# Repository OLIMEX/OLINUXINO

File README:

OLinuXino - Single-Board Linux Computer, Copyright (C) 2012-2019, OLIMEX Ltd

THE PROJECT:

OLinuXino is an Open Source Software and Open Source Hardware project, aiming to produce low cost (starting from EUR 24)
Linux and Android Single Board Computers (SBC) in both commercial and industrial temperature range. Board variants with extra flash memory
are also available.

People keep comparing OLinuXino with Raspberry Pi and BeagleBone project, so we would like to state some of the differences here:

Although the projects are similar there are different goals and implementations:

OLINUXINO is completely open source - including hardware and software, this means you have access to all CAD files and sources and you
can reuse them for your own personal or commercial project. There are NO restrictions to manufacture and sell these board for your own 
use or resale, just keep credits that your board is based on OLinuXino design and make sure to change the silkscreen to not confuse people that you are selling original OLinuXino.

iMX233-OLINUXINO use widely available microcontroller iMX233 which cost USD 5.50 in 100 pcs quantity, this means that people can spin 
off their own boards and manufacture them cheap as the processor is in TQFP easy to assembly by hobbyist package.

RASPBERRY PI have not released CAD files nor complete schematics, RPi uses processor from Broadcom which is not available for sale in 
small quantity, it uses BGA package which require expensive setup to assembly. RPi is designed to be home gadget, OLINUXINO viarnatns
can work in industrial environment -25+85C and are designed to be low cost but NOISE immune.

BeagleBone have open source CAD hardware files but uses BGA processor and BB board is very complex and hard to manufacture in small 
quantities.

iMX233-OLINUXINO uses processor on 454Mhz and have less memory and will not allow fancy graphics, but this is not our intention.

To name few potential applications for OLINUXINO:

- 3D rep-rap printer controller including G-code interpreter - now all 3D printers use PC/Laptop connected to Arduino stepper driver, this board will handle both without problem
- Low cost PLC running open source PLC programming languages
- Home Automation - connecting GSM module or Zigbee sensors would be easy with the existing UEXT connector
- OLINUXINO has 100Mbit Ethernet port, but there are many low cost $10 WIFI USB modules with Linux drivers like RTL8192 which allow OLINUXINO to connect to internet wireless and to may control relays and sensors without need for LAN wiring.
- Having small linux module with GPIOs would be handy even to embed it in other products. BeagleBone do not allow the board to be used in commercial projects, there are no restrictions with OLINUXINO

THE DEVELOPMENT PATH:

Step 1:
OLinuXino project started with iMX233 from Freescale for several reasons: this is ARM9 processor running at 454Mhz with enough power to run linux and still in handsolder friendly TQFP package, which allow hobby DIY approach. iMX233-OLinuXino-MICRO is even on 2 layer PCB and running at full speed. The maximum memory of 64MB though limited the applications with it, so we were looking around for something more powerful when A13 from Allwinner came along.

Step 2:
A13 is Cortex-A8 processor which can address up to 512MB RAM and run at 1GHz. The best of all it again comes in the hand soldering friendly TQFP package (actually it's the first and the only Cortex-A8 in TQFP package). So designing A13-OLinuXino was the next logical step. The first prototypes are already produced and everything works as expected. A13-OLinuXino production is scheduled for September.
A13-OLinuXino have 512MB RAM, 4 USB hosts (1 dedicated for WIFI), 1 USB-OTG, Audio out, Audio in, SD-card, VGA, buttons, 72 GPIOs, LCD connector

Step 3:
A10 is the big brother of A13 it's also Cortex-A8 running at 1Ghz (many Chinese tablet/set-top-box vendors write it's 1.2 or 1.5GHz but this is overclocking and same is possible with A13 too, but not recommended for normal operation). It can address up to 2GB of RAM, and on top of A13 have SATA, HDMI, VGA and composite video outputs + much more GPIOs as it's in BGA442 package. While we developed A13-OLinuXino we got many requests for hackable A10 board as all current solutions are tablets or set-top-boxes which are not designed to have GPIO connectors and to allow hardware hacking
A10-OLinuXino will have same as A13 but including more GPIOs, 1GB RAM, HDMI, SATA and 100MBit Ethernet

Step 4:
A10S is new processor from Allwinner with Ethernet and HDMI. Low cost board with A10S Cortex-A8 @ 1GHz + 512MB RAM + Ethernet 100Mbit + USB Host/USB-OTG + SD-card + SD-MMC card + HDMI is released.

Step 5:
A20 is Dual Core Cortex-A7 processor which is almost pin to pin compatible, so A10 board can work with A20 processors too. We have low cost A20 board prototypes working and A20-SOM work in progress.

Step 6:
Texas Instruments Sitara AM3352 processor is necessary for Industrial customers who want a longevity supply program, TI as Freescale guarantee that when start producing processor continue the production at least 5-10 years, this way customers are not forced to change their designs every year. So we work on AM3352 module with: AM3352 720Mhz, Cortex-A8 processor, 512MB DDR3 RAM (optional we will make 1GB RAM version also), power supply 6-16VDC, x4 USB 2.0 hosts, 100Mbit Ethernet, SD-card, VGA, CAN, GPIO connector, LCD connector with touchscreen to work with A13-LCD7TS and A13-43TS LCDs, UEXT connector, JTAG.

Step 7:
Allwinner A64 chip into A64-OLinuXino development board.

Step 8:
DIY laptop TERES-I with A64 chip.

Step 9:
RT5350F-OLinuXino first MIPS OLinuXino with Ralink RT5350 
S3-OLinuXino camera linux board with Allwinner S3 SOC
STM32MP15X-OLinuXino-LIME2 - board with same layout as A20-OLinuXino-LIME2 but with STM new DUal Core Cortex-A7 processor STM32MP157
iMX8QM-TUKHLA - OLinuXino board with most powerful NXP iMX8 processor QUAD MAX with Dual core Cortex-A72 and Quad code Cortex-A53 

Step 10:
... we don't know yet, there are lot of candidates, but we start to become a little picky. To start the development of new OSHW OLinuXino board we will look at least the SOC to have proper Linux Support as we are really overwhelmed of the tons of new SOCs released with just Android and binary blobs.
Rockchip is doing a very good job recently releasing mainline Linux support for their devices.

WEB RESOURCES:

http://www.olimex.com - OLIMEX Ltd web site where the OLinuXino board info is hosted

https://github.com/OLIMEX/OLINUXINO - GitHub web site hosting the Hardware and Software sources

https://www.olimex.com/forum/index.php - Olimex forum for OLinuXino project discussions

OLinuXino IRC channel: join #olimex on irc.freenode.net , alternatively use http://webchat.freenode.net/?channels=olimex for web IRC chat

LICENSEE:

HARDWARE
The Hardware project is released under the Creative Commons Attribution-Share Alike 3.0 United States License.
You may reproduce it for both your own personal use, and for commercial use. 
You will have to provide a link to the original creator of the project http://www.olimex.com on any documentation or website.
You may also modify the files, but you must then release them as well under the same terms.
Credit can be attributed through a link to the creator website: http://www.olimex.com
You should alter the silkscreen to not confuse people who buy your product that they buy the original OLinuXino made by Olimex.

SOFTWARE
The software is released under GPL3.

DOCUMENTATION
The documentation is released under the Creative Commons Attribution-Share Alike 3.0 United States License.

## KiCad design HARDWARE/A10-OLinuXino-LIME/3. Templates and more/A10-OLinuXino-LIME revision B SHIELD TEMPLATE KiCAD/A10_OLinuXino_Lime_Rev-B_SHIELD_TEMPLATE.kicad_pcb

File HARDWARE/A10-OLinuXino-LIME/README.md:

## Olimex A10-OLinuXino-LIME hardware sources

## Product page: https://www.olimex.com/Products/OLinuXino/A10/A10-OLinuXino-LIME/open-source-hardware

## A20-OLINUXINO-LIME AND A10-OLINUXINO-LIME SHARE SAME HARDWARE LAYOUT. 

### FOR LATEST HARDWARE REVISION, PLEASE VISIT THE A20-OLINUXINO-LIME HARDWARE SECTION: 

### https://github.com/OLIMEX/OLINUXINO/tree/master/HARDWARE/A20-OLinuXino-LIME

### THE A10 AND A20 CHIPS ARE PIN-TO-PIN COMPATIBLE (DROP-IN REPLACEABLE). ONLY THE MAIN CHIP PLACED IS DIFFERENT.

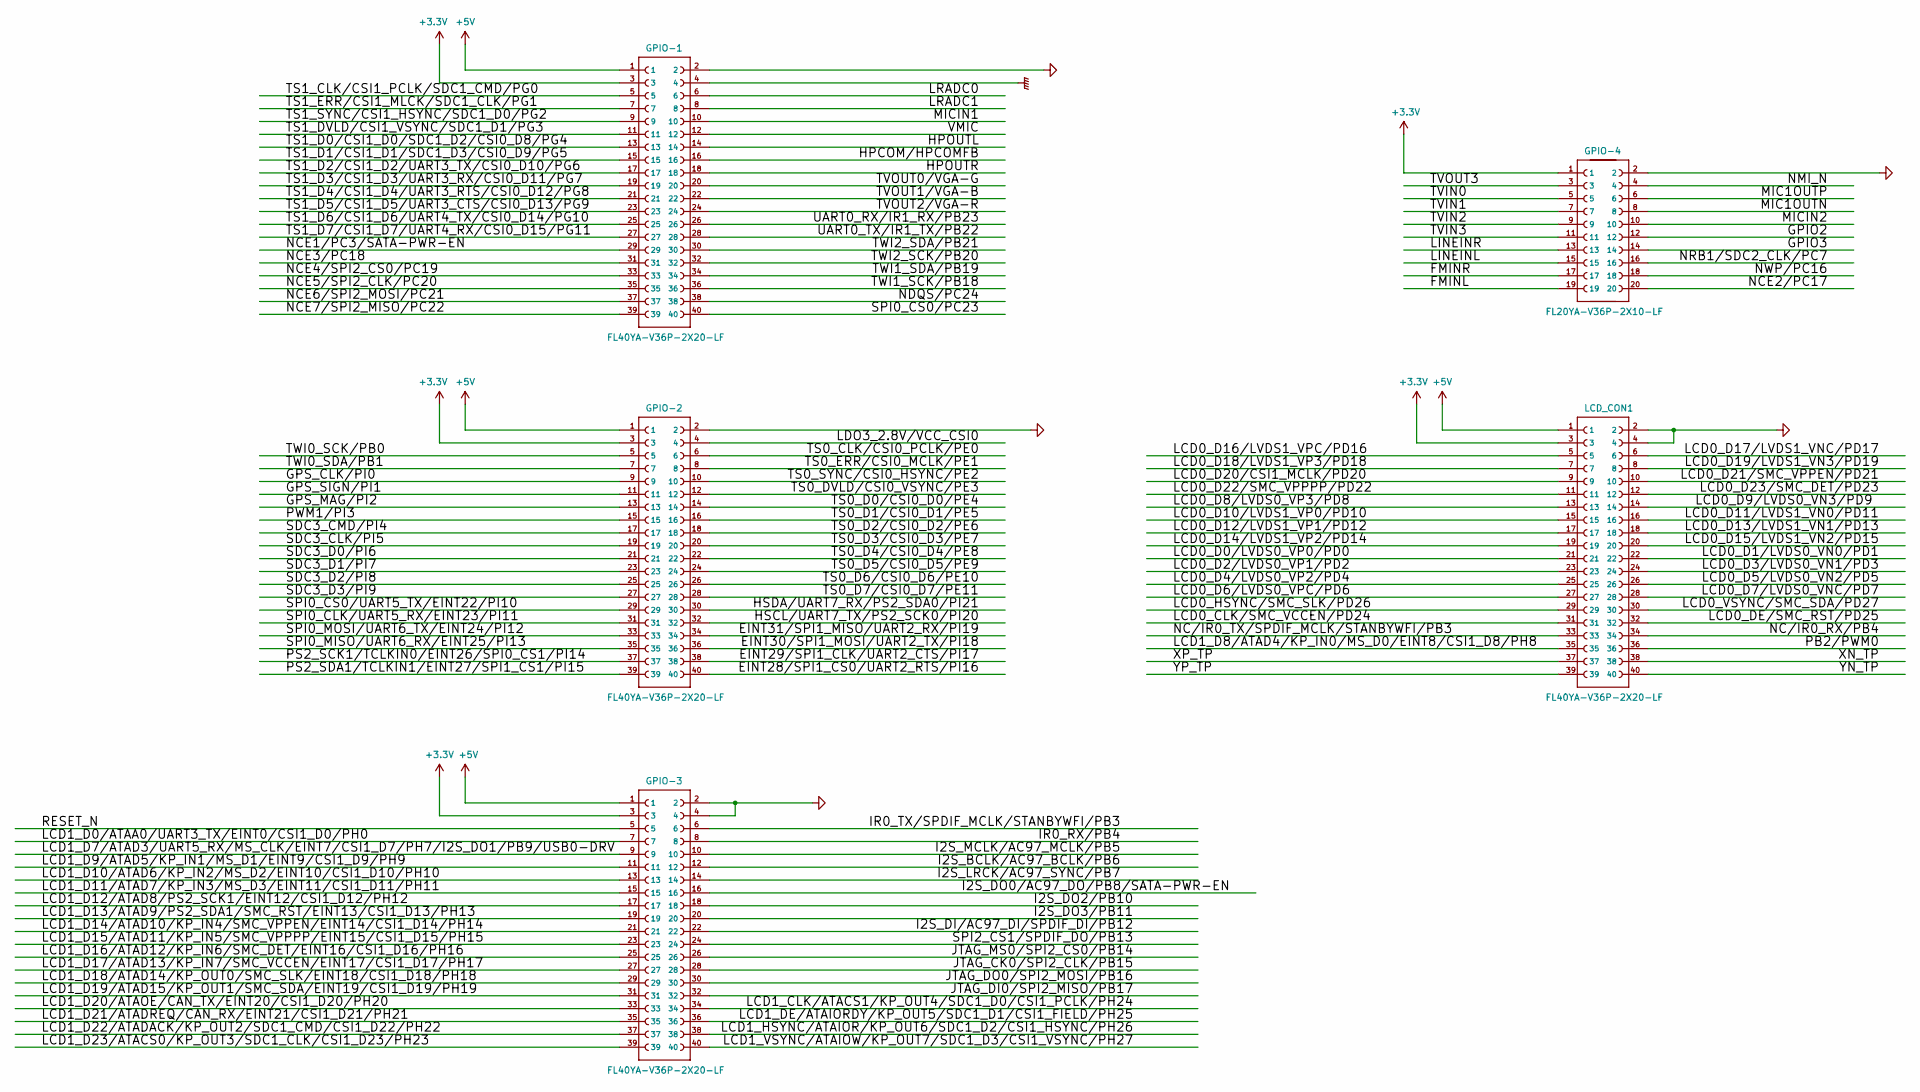
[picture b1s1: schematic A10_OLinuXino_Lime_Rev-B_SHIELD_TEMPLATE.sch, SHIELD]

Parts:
GPIO-1, GPIO-2, GPIO-3: FL40YA-V36P-2X20-LF; A10_OLIMEXINO_LIME_SHIELD_1-YA-V36P-2X20-LF
GPIO-4: FL20YA-V36P-2X10-LF; A10_OLIMEXINO_LIME_SHIELD_1-YA-V36P-2X10-LF
LCD_CON1: FL40YA-V36P-2X20-LF; A10_OLIMEXINO_LIME_SHIELD_1-YA-V36P-2X20-LF

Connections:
+3V3: GPIO-1.3, GPIO-2.3, GPIO-3.3, GPIO-4.1, LCD_CON1.3
+5V: GPIO-1.1, GPIO-2.1, GPIO-3.1, LCD_CON1.1
/EINT28/SPI1_CS0/UART2_RTS/PI16: GPIO-2.40
/EINT29/SPI1_CLK/UART2_CTS/PI17: GPIO-2.38
/EINT30/SPI1_MOSI/UART2_TX/PI18: GPIO-2.36
/EINT31/SPI1_MISO/UART2_RX/PI19: GPIO-2.34
/FMINL: GPIO-4.19
/FMINR: GPIO-4.17
/GPIO2: GPIO-4.12
/GPIO3: GPIO-4.14
/GPS_CLK/PI0: GPIO-2.9
/GPS_MAG/PI2: GPIO-2.13
/GPS_SIGN/PI1: GPIO-2.11
/HPCOM/HPCOMFB: GPIO-1.16
/HPOUTL: GPIO-1.14
/HPOUTR: GPIO-1.18
/HSCL/UART7_TX/PS2_SCK0/PI20: GPIO-2.32
/HSDA/UART7_RX/PS2_SDA0/PI21: GPIO-2.30
/I2S_BCLK/AC97_BCLK/PB6: GPIO-3.12
/I2S_DI/AC97_DI/SPDIF_DI/PB12: GPIO-3.22
/I2S_DO0/AC97_DO/PB8/SATA-PWR-EN: GPIO-3.16
/I2S_DO2/PB10: GPIO-3.18
/I2S_DO3/PB11: GPIO-3.20
/I2S_LRCK/AC97_SYNC/PB7: GPIO-3.14
/I2S_MCLK/AC97_MCLK/PB5: GPIO-3.10
/IR0_RX/PB4: GPIO-3.8
/IR0_TX/SPDIF_MCLK/STANBYWFI/PB3: GPIO-3.6
/JTAG_CK0/SPI2_CLK/PB15: GPIO-3.28
/JTAG_DI0/SPI2_MISO/PB17: GPIO-3.32
/JTAG_DO0/SPI2_MOSI/PB16: GPIO-3.30
/JTAG_MS0/SPI2_CS0/PB14: GPIO-3.26
/LCD0_CLK/SMC_VCCEN/PD24: LCD_CON1.31
/LCD0_D0/LVDS0_VP0/PD0: LCD_CON1.21
/LCD0_D1/LVDS0_VN0/PD1: LCD_CON1.22
/LCD0_D2/LVDS0_VP1/PD2: LCD_CON1.23
/LCD0_D3/LVDS0_VN1/PD3: LCD_CON1.24
/LCD0_D4/LVDS0_VP2/PD4: LCD_CON1.25
/LCD0_D5/LVDS0_VN2/PD5: LCD_CON1.26
/LCD0_D6/LVDS0_VPC/PD6: LCD_CON1.27
/LCD0_D7/LVDS0_VNC/PD7: LCD_CON1.28
/LCD0_D8/LVDS0_VP3/PD8: LCD_CON1.13
/LCD0_D9/LVDS0_VN3/PD9: LCD_CON1.14
/LCD0_D10/LVDS1_VP0/PD10: LCD_CON1.15
/LCD0_D11/LVDS1_VN0/PD11: LCD_CON1.16
/LCD0_D12/LVDS1_VP1/PD12: LCD_CON1.17
/LCD0_D13/LVDS1_VN1/PD13: LCD_CON1.18
/LCD0_D14/LVDS1_VP2/PD14: LCD_CON1.19
/LCD0_D15/LVDS1_VN2/PD15: LCD_CON1.20
/LCD0_D16/LVDS1_VPC/PD16: LCD_CON1.5
/LCD0_D17/LVDS1_VNC/PD17: LCD_CON1.6
/LCD0_D18/LVDS1_VP3/PD18: LCD_CON1.7
/LCD0_D19/LVDS1_VN3/PD19: LCD_CON1.8
/LCD0_D20/CSI1_MCLK/PD20: LCD_CON1.9
/LCD0_D21/SMC_VPPEN/PD21: LCD_CON1.10
/LCD0_D22/SMC_VPPPP/PD22: LCD_CON1.11
/LCD0_D23/SMC_DET/PD23: LCD_CON1.12
/LCD0_DE/SMC_RST/PD25: LCD_CON1.32
/LCD0_HSYNC/SMC_SLK/PD26: LCD_CON1.29
/LCD0_VSYNC/SMC_SDA/PD27: LCD_CON1.30
/LCD1_CLK/ATACS1/KP_OUT4/SDC1_D0/CSI1_PCLK/PH24: GPIO-3.34
/LCD1_D0/ATAA0/UART3_TX/EINT0/CSI1_D0/PH0: GPIO-3.7
/LCD1_D7/ATAD3/UART5_RX/MS_CLK/EINT7/CSI1_D7/PH7/I2S_DO1/PB9/USB0-DRV: GPIO-3.9
/LCD1_D8/ATAD4/KP_IN0/MS_D0/EINT8/CSI1_D8/PH8: LCD_CON1.35
/LCD1_D9/ATAD5/KP_IN1/MS_D1/EINT9/CSI1_D9/PH9: GPIO-3.11
/LCD1_D10/ATAD6/KP_IN2/MS_D2/EINT10/CSI1_D10/PH10: GPIO-3.13
/LCD1_D11/ATAD7/KP_IN3/MS_D3/EINT11/CSI1_D11/PH11: GPIO-3.15
/LCD1_D12/ATAD8/PS2_SCK1/EINT12/CSI1_D12/PH12: GPIO-3.17
/LCD1_D13/ATAD9/PS2_SDA1/SMC_RST/EINT13/CSI1_D13/PH13: GPIO-3.19
/LCD1_D14/ATAD10/KP_IN4/SMC_VPPEN/EINT14/CSI1_D14/PH14: GPIO-3.21
/LCD1_D15/ATAD11/KP_IN5/SMC_VPPPP/EINT15/CSI1_D15/PH15: GPIO-3.23
/LCD1_D16/ATAD12/KP_IN6/SMC_DET/EINT16/CSI1_D16/PH16: GPIO-3.25
/LCD1_D17/ATAD13/KP_IN7/SMC_VCCEN/EINT17/CSI1_D17/PH17: GPIO-3.27
/LCD1_D18/ATAD14/KP_OUT0/SMC_SLK/EINT18/CSI1_D18/PH18: GPIO-3.29
/LCD1_D19/ATAD15/KP_OUT1/SMC_SDA/EINT19/CSI1_D19/PH19: GPIO-3.31
/LCD1_D20/ATAOE/CAN_TX/EINT20/CSI1_D20/PH20: GPIO-3.33
/LCD1_D21/ATADREQ/CAN_RX/EINT21/CSI1_D21/PH21: GPIO-3.35
/LCD1_D22/ATADACK/KP_OUT2/SDC1_CMD/CSI1_D22/PH22: GPIO-3.37
/LCD1_D23/ATACS0/KP_OUT3/SDC1_CLK/CSI1_D23/PH23: GPIO-3.39
/LCD1_DE/ATAIORDY/KP_OUT5/SDC1_D1/CSI1_FIELD/PH25: GPIO-3.36
/LCD1_HSYNC/ATAIOR/KP_OUT6/SDC1_D2/CSI1_HSYNC/PH26: GPIO-3.38
/LCD1_VSYNC/ATAIOW/KP_OUT7/SDC1_D3/CSI1_VSYNC/PH27: GPIO-3.40
/LDO3_2.8V/VCC_CSI0: GPIO-2.4
/LINEINL: GPIO-4.15
/LINEINR: GPIO-4.13
/LRADC0: GPIO-1.6
/LRADC1: GPIO-1.8
/MIC1OUTN: GPIO-4.8
/MIC1OUTP: GPIO-4.6
/MICIN1: GPIO-1.10
/MICIN2: GPIO-4.10
/NC/IR0_RX/PB4: LCD_CON1.34
/NC/IR0_TX/SPDIF_MCLK/STANBYWFI/PB3: LCD_CON1.33
/NCE1/PC3/SATA-PWR-EN: GPIO-1.29
/NCE2/PC17: GPIO-4.20
/NCE3/PC18: GPIO-1.31
/NCE4/SPI2_CS0/PC19: GPIO-1.33
/NCE5/SPI2_CLK/PC20: GPIO-1.35
/NCE6/SPI2_MOSI/PC21: GPIO-1.37
/NCE7/SPI2_MISO/PC22: GPIO-1.39
/NDQS/PC24: GPIO-1.38
/NMI_N: GPIO-4.4
/NRB1/SDC2_CLK/PC7: GPIO-4.16
/NWP/PC16: GPIO-4.18
/PB2/PWM0: LCD_CON1.36
/PS2_SCK1/TCLKIN0/EINT26/SPI0_CS1/PI14: GPIO-2.37
/PS2_SDA1/TCLKIN1/EINT27/SPI1_CS1/PI15: GPIO-2.39
/PWM1/PI3: GPIO-2.15
/RESET_N: GPIO-3.5
/SDC3_CLK/PI5: GPIO-2.19
/SDC3_CMD/PI4: GPIO-2.17
/SDC3_D0/PI6: GPIO-2.21
/SDC3_D1/PI7: GPIO-2.23
/SDC3_D2/PI8: GPIO-2.25
/SDC3_D3/PI9: GPIO-2.27
/SPI0_CLK/UART5_RX/EINT23/PI11: GPIO-2.31
/SPI0_CS0/PC23: GPIO-1.40
/SPI0_CS0/UART5_TX/EINT22/PI10: GPIO-2.29
/SPI0_MISO/UART6_RX/EINT25/PI13: GPIO-2.35
/SPI0_MOSI/UART6_TX/EINT24/PI12: GPIO-2.33
/SPI2_CS1/SPDIF_DO/PB13: GPIO-3.24
/TS0_CLK/CSI0_PCLK/PE0: GPIO-2.6
/TS0_D0/CSI0_D0/PE4: GPIO-2.14
/TS0_D1/CSI0_D1/PE5: GPIO-2.16
/TS0_D2/CSI0_D2/PE6: GPIO-2.18
/TS0_D3/CSI0_D3/PE7: GPIO-2.20
/TS0_D4/CSI0_D4/PE8: GPIO-2.22
/TS0_D5/CSI0_D5/PE9: GPIO-2.24
/TS0_D6/CSI0_D6/PE10: GPIO-2.26
/TS0_D7/CSI0_D7/PE11: GPIO-2.28
/TS0_DVLD/CSI0_VSYNC/PE3: GPIO-2.12
/TS0_ERR/CSI0_MCLK/PE1: GPIO-2.8
/TS0_SYNC/CSI0_HSYNC/PE2: GPIO-2.10
/TS1_CLK/CSI1_PCLK/SDC1_CMD/PG0: GPIO-1.5
/TS1_D0/CSI1_D0/SDC1_D2/CSI0_D8/PG4: GPIO-1.13
/TS1_D1/CSI1_D1/SDC1_D3/CSI0_D9/PG5: GPIO-1.15
/TS1_D2/CSI1_D2/UART3_TX/CSI0_D10/PG6: GPIO-1.17
/TS1_D3/CSI1_D3/UART3_RX/CSI0_D11/PG7: GPIO-1.19
/TS1_D4/CSI1_D4/UART3_RTS/CSI0_D12/PG8: GPIO-1.21
/TS1_D5/CSI1_D5/UART3_CTS/CSI0_D13/PG9: GPIO-1.23
/TS1_D6/CSI1_D6/UART4_TX/CSI0_D14/PG10: GPIO-1.25
/TS1_D7/CSI1_D7/UART4_RX/CSI0_D15/PG11: GPIO-1.27
/TS1_DVLD/CSI1_VSYNC/SDC1_D1/PG3: GPIO-1.11
/TS1_ERR/CSI1_MLCK/SDC1_CLK/PG1: GPIO-1.7
/TS1_SYNC/CSI1_HSYNC/SDC1_D0/PG2: GPIO-1.9
/TVIN0: GPIO-4.5
/TVIN1: GPIO-4.7
/TVIN2: GPIO-4.9
/TVIN3: GPIO-4.11
/TVOUT0/VGA-G: GPIO-1.20
/TVOUT1/VGA-B: GPIO-1.22
/TVOUT2/VGA-R: GPIO-1.24
/TVOUT3: GPIO-4.3
/TWI0_SCK/PB0: GPIO-2.5
/TWI0_SDA/PB1: GPIO-2.7
/TWI1_SCK/PB18: GPIO-1.36
/TWI1_SDA/PB19: GPIO-1.34
/TWI2_SCK/PB20: GPIO-1.32
/TWI2_SDA/PB21: GPIO-1.30
/UART0_RX/IR1_RX/PB23: GPIO-1.26
/UART0_TX/IR1_TX/PB22: GPIO-1.28
/VMIC: GPIO-1.12
/XN_TP: LCD_CON1.38
/XP_TP: LCD_CON1.37
/YN_TP: LCD_CON1.40
/YP_TP: LCD_CON1.39
GND: GPIO-1.2, GPIO-2.2, GPIO-3.2, GPIO-3.4, GPIO-4.2, LCD_CON1.2, LCD_CON1.4
GNDPWR: GPIO-1.4

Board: 2 copper layers, 5 parts (5 on the bottom side), 3 nets, no tracks yet.

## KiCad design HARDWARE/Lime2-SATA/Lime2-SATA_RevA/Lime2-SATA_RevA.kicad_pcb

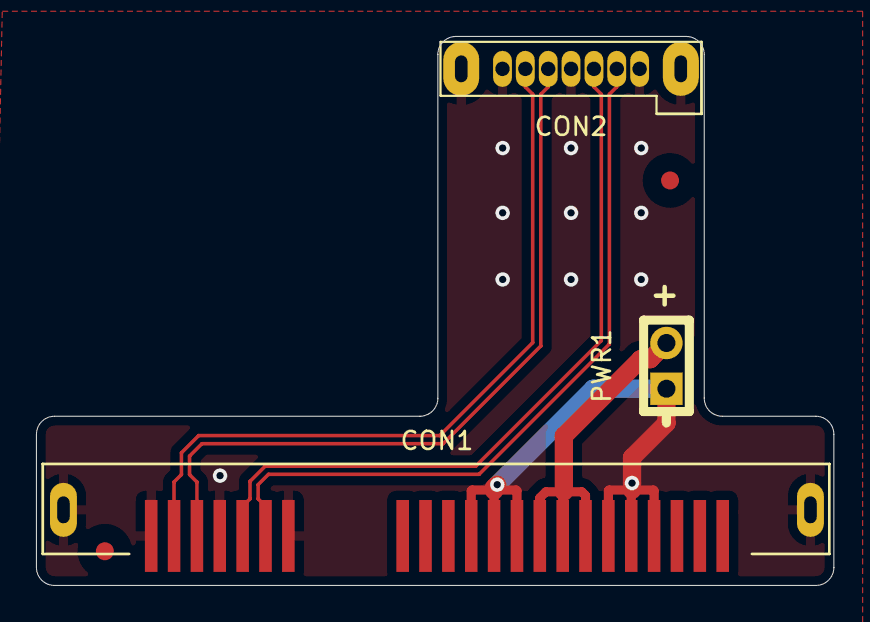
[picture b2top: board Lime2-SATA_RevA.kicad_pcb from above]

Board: 2 copper layers, 44.3 x 30.5 mm, 5 parts (0 on the bottom side), 6 nets.

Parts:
CON1: SATA7_15P; SATA7_15_HDD
CON2: SATA7P; SATA7-S-PTH
PWR1: BH02S; SIP2
Ref*: Val**; Fiducial1x3_transp
Ref*#2: Val**; Fiducial1x3_transp

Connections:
/GND: CON1.0, CON1.1, CON1.4, CON1.7, CON1.14, CON1.15, CON1.16, CON1.20, CON1.21, CON1.22, CON2.0, CON2.1, CON2.4, CON2.7, PWR1.1
/RX_N: CON1.5, CON2.5
/RX_P: CON1.6, CON2.6
/TX_N: CON1.3, CON2.3
/TX_P: CON1.2, CON2.2
unnamed: CON1.17, CON1.18, CON1.19, PWR1.2

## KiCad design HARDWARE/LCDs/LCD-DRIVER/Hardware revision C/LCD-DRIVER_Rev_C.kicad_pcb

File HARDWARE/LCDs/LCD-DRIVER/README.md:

LCD-DRIVER is a common LCD board used in Olimex displays that have one of these suffixes 
at the end of the product name: "-RTS", "-CTS", or "+" and suffix.

Displays without touchscreen, without "+" at the end of the product name, or with suffix "TS" 
use own driver boards, not LCD-DRIVER. Check the folders of these displays for schematics of 
the driver boards.

It is important to notice that depending on the size of the display and the type of touschreen 
used the LCD_DRIVER board would be configured dirrently. Refer to the labes in the schematic 
and also refer to the bill of materials in the hardware revision B folder (BOM) for the 
different configurations.

List of boards using LCD-DRIVER as of 03.09.2019:

LCD-OLinuXino-4.3+
LCD-OLinuXino-4.3RTS
LCD-OLinuXino-5CTS+
LCD-OLinuXino-7+
LCD-OLinuXino-7CTS
LCD-OLinuXino-7RTS
LCD-OLinuXino-7TS+
LCD-OLinuXino-10+
LCD-OLinuXino-10CTS
LCD-OLinuXino-10RTS
LCD-OLinuXino-10TS+

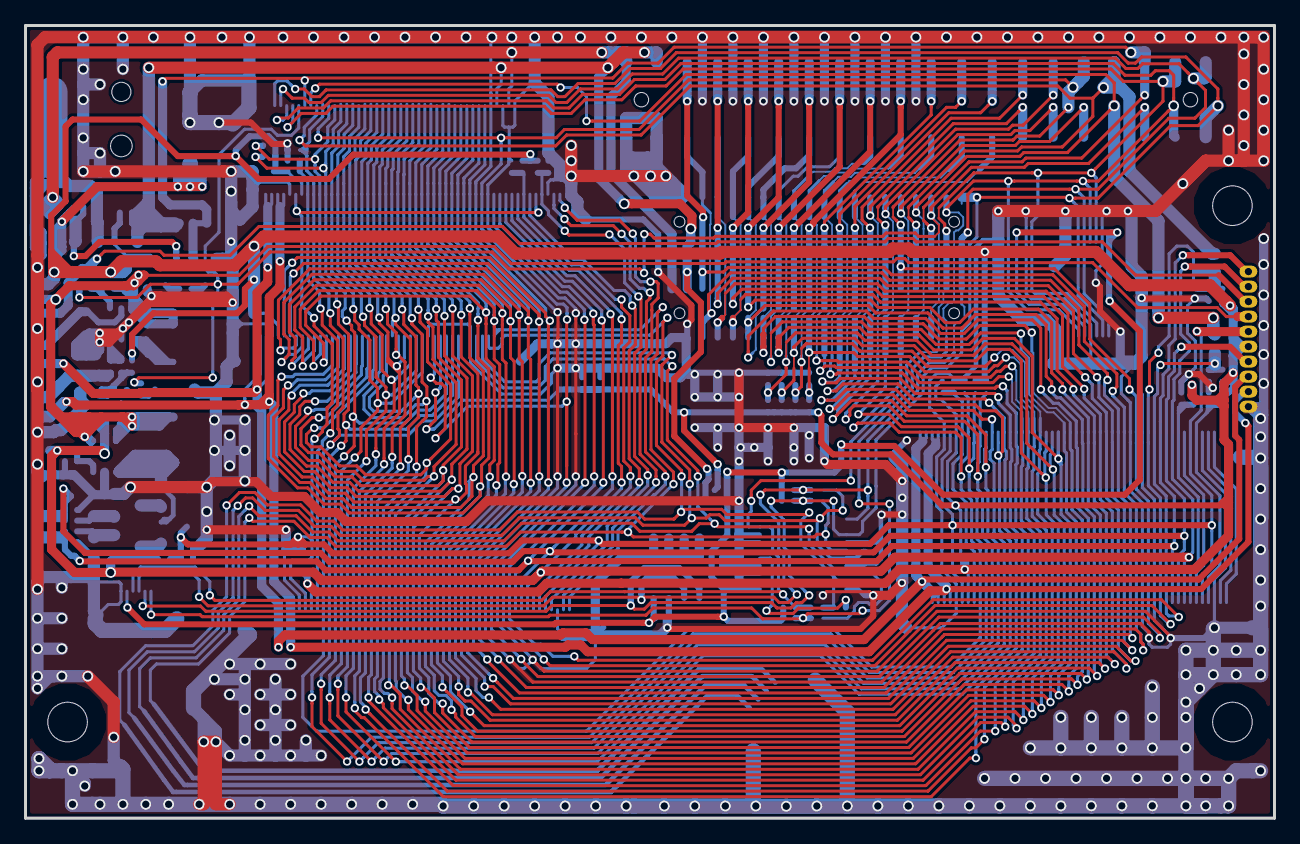
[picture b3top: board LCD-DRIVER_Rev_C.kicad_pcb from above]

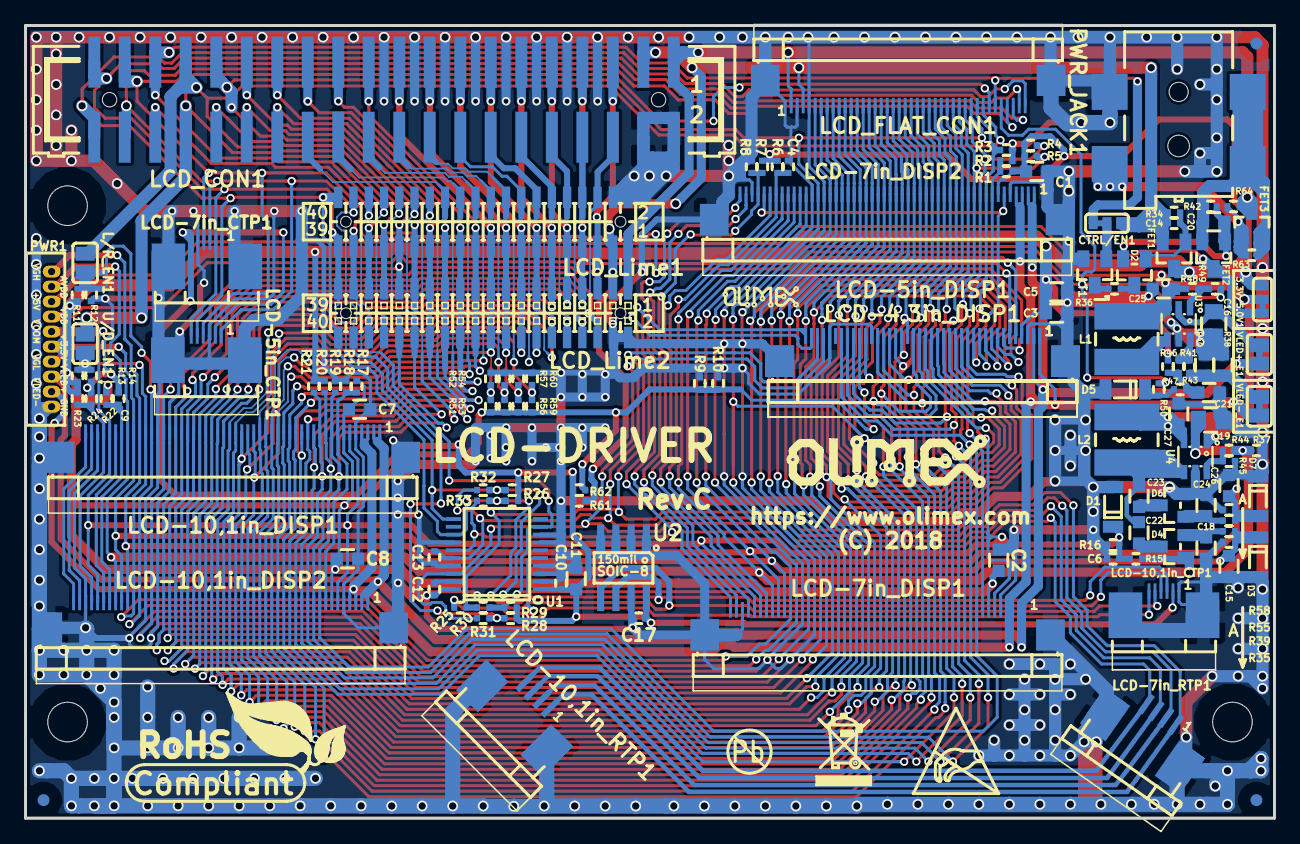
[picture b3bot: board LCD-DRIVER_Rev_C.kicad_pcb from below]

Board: 2 copper layers, 104.0 x 66.0 mm, 143 parts (140 on the bottom side), 88 nets.

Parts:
3.3V/5.0V1: 3.3V:Opened/5.0V:Closed; SJ_2_SMALL_23_TIED
C1, C2, C5, C7, C8, C27: NA(22uF/6.3V/20%/X5R/C0603); C_0603_5MIL_DWS
C3, C11, C20, C21, C25: 22uF/6.3V/20%/X5R/C0603; C_0603_5MIL_DWS
C4, C6, C9: NA(100nF/16V/10%/X7R/C0402); C_0402_5MIL_DWS
C10, C14, C17: 100nF/16V/10%/X7R/C0402; C_0402_5MIL_DWS
C12, C13: 10nF/50V/10%/X7R/C0402; C_0402_5MIL_DWS
C15, C18, C22, C23, C24, C26: NA(100nF/50V/20%/Y5V/C0603); C_0603_5MIL_DWS
C16: 2.2uF/50V/10%/X5R/C0805; C_0805_5MIL_DWS
C19: NA(2.2uF/50V/10%/X5R/C0805); C_0805_5MIL_DWS
CTRL/EN1: CTRL:Closed/EN:Opened; SJ_2_SMALL_23_TIED
D1: NA(BZV55C3V9/SOD80C); SOD80C-4148-KA
D2: BAT54C(SOT23-3); SOT23-3
D3: NA(BZV55C20/SOD80C); SOD80C-4148-KA
D4, D6: NA(BAT54S(SOT23-3)); SOT23-3
D5: NA(BZV55C3V6/SOD80C); SOD80C-4148-KA
D7: NA(BZV55C5V1/SOD80C); SOD80C-4148-KA
FET1, FET2, FET3: IRLML6402(SOT23-3); SOT23
FID1, FID2, FID3: Fiducial; Fiducial1x3
L1: 22uH/1.5A/220mR/20%/CD53(YS53-220M); CD53(54)
L2: NA(22uH/1.5A/220mR/20%/CD53(YS53-220M)); CD53(54)
L/R_EN1: Opened; SJ
LCD-4,3in_DISP1: LCD-4.3"(480x272_GFT043HA480272Y)+(FPV-WZA21-40-L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; FPV-WZA21-40-LF
LCD-5in_CTP1: NA(LCD-5”(CAPACITIVE_TS)+(FPV-WZB201-06-LF)); FPV-WZB201-06-LF
LCD-5in_DISP1: NA(LCD-5”(800x480_HDW050TN22)+(FPV-WZA21-40-LF)); FPV-WZA21-40-LF
LCD-7in_CTP1, LCD-10,1in_CTP1: NA(FPV-WZB201-06-LF); FPV-WZB201-06-LF
LCD-7in_DISP1: NA(LCD-7"(800x480_AT070TN92)+(FPV-WZA21-50-LF)); FPV-WZA21-50-LF
LCD-7in_DISP2: NA(LCD-7"(800x480_CX700TN94-CTP38)+(FPV-WZA21-50-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; FPV-WZA21-50-LF
LCD-7in_RTP1: NA(LCD-TS7(LCD-7"_TOUCHPANEL)+(FPA-WZB25-04-LF)); FPA-WZB25-04-LF
LCD-10,1in_DISP1: NA(LCD-10"(1024x600_LOYE_BOE10.1-33LEDH)+(FPV-WZA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; FPV-WZA21-50-LF
LCD-10,1in_DISP2: NA(LCD-10"_CAP_TS(1024x600_IPS_CXT101H39-42E)+(FP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; FPV-WZA21-50-LF
LCD-10,1in_RTP1: NA(LCD-TS10(LCD-10"_TOUCHPANEL)+(FPA-WZB25-04-LF)); FPA-WZB25-04-LF
LCD_CON1: GBH254SMT-40(B-V-40-LF); GBH254SMT-40
LCD_FLAT_CON1: FPV-WZA21-40-LF
LCD_Lime1: MALE-PAV16X-2x20(0.8_bud); GPCB127SMT-02X20(YA-V36P-2X20-LF)_Drill_0.9mm
LCD_Lime2: MALE-PAV16X-2x20(0.8_bud); GPH127SMT-02X20(PA-V16X-2X20-LF)_Drill_0.9mm
Logo-Olimex-Big: OLIMEX_LOGO_TB
Logo-Olimex_Small: LOGO_OLIMEX_80
MountingHole*: Mounting_hole_3.3mm
MountingHole*#2, MountingHole*#3: Mounting_hole_3.3mm
PWR1: NA(WU10S); WU10S
PWR_JACK1: PWRJ-2mm(DCJ-W54R-20-LF)
R1, R4, R5, R8, R12, R13, R17, R20, R21, R24, R49, R62: NA/R0402; R_0402_5MIL_DWS
R2, R3, R6, R7, R10, R11, R14, R18, R19, R22, R23, R51, R52, R53, R54, R56, R57, R59, R60, R64: NA(10k/R0402); R_0402_5MIL_DWS
R9, R34, R42, R48, R63: 10k/R0402; R_0402_5MIL_DWS
R15, R39, R55: NA(1k/1%/R0402); R_0402_5MIL_DWS
R16: NA(560R/1%/R0402); R_0402_5MIL_DWS
R25, R43: 20k/1%/R0402; R_0402_5MIL_DWS
R26, R27, R28, R29, R41: 2.2k/R0402; R_0402_5MIL_DWS
R30, R31, R32, R33: NA(0R/R0402); R_0402_5MIL_DWS
R35, R37, R58: NA(20k/1%/R0402); R_0402_5MIL_DWS
R36: 1k/1%/R0402; R_0402_5MIL_DWS
R38: 4.7R/1%/R0603; R_0603_5MIL_DWS
R40: NA/R0603; R_0603_5MIL_DWS
R44: NA(56.2k/1%/R0402); R_0402_5MIL_DWS
R45: NA(1.05k/1%/R0402); R_0402_5MIL_DWS
R46, R47: 27k/R0402; R_0402_5MIL_DWS
R50: 220R/R0402; R_0402_5MIL_DWS
R61: 0R/R0402; R_0402_5MIL_DWS
Sign-Antistatic: Val**; LOGO_ANTISTATIC_1
Sign-PB_Free: LOGO_PBFREE
Sign-RecycleBin: LOGO_RECYCLEBIN_1
Sign-RoHS_Compliant: Val**; LOGO_ROHS_1
T1: DTC114YKA(SOT-23); SOT23
U1: AR1021T-I_SS(SSOP-20); SSOP-20W
U2: AT24C16C-SSHM-T(SOIC-8_150mil); SOIC-8_150mil
U3: AP3036BKTR-G1(SOT23-6); SOT23-6
U4: NA(AP3036BKTR-G1(SOT23-6)); SOT23-6
U/D_EN1: Opened; SJ
VLED+_E1: Closed; SJ_Closed
VLED-_E1: Closed; SJ_Closed

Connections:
+3.3VA: C10.2, C11.1, C17.1, LCD-5in_CTP1.2, LCD-7in_CTP1.6, LCD-10,1in_CTP1.2, R26.2, R27.2, R28.2, R29.2, R61.1, R62.2, U1.1, U2.8
+3V3: 3.3V/5.0V1.1, C1.1, C2.1, C3.1, C5.1, C7.1, C8.1, FET1.3, LCD-4,3in_DISP1.4, LCD-4,3in_DISP1.31, LCD-5in_DISP1.4, LCD-5in_DISP1.31, LCD-7in_DISP1.7, LCD-7in_DISP2.7, LCD-10,1in_DISP1.7, LCD-10,1in_DISP2.7, PWR1.6, R1.1, R4.1, R5.1, R6.1, R7.1, R9.2, R10.2, R11.2, R13.2, R17.1, R20.1, R21.1, R22.1, R23.1, R46.1, R51.1, R53.1, R56.1, R59.1, R62.1
+5V: 3.3V/5.0V1.3, FET2.3, PWR1.3
/LCD_3.3V: C14.1, CTRL/EN1.1, FET1.2, LCD_CON1.3, LCD_FLAT_CON1.3, LCD_Lime1.3, LCD_Lime2.3, R34.2, R61.2
/LCD_5.0V: FET3.3, LCD_CON1.1, LCD_FLAT_CON1.1, LCD_Lime1.1, LCD_Lime2.1, R64.2
/LCD_B0: LCD-4,3in_DISP1.21, LCD-5in_DISP1.21, LCD-7in_DISP1.19, LCD-7in_DISP2.19, LCD-10,1in_DISP1.19, LCD-10,1in_DISP2.19, LCD_CON1.21, LCD_FLAT_CON1.21, LCD_Lime1.21, LCD_Lime2.21
/LCD_B1: LCD-4,3in_DISP1.22, LCD-5in_DISP1.22, LCD-7in_DISP1.18, LCD-7in_DISP2.18, LCD-10,1in_DISP1.18, LCD-10,1in_DISP2.18, LCD_CON1.22, LCD_FLAT_CON1.22, LCD_Lime1.22, LCD_Lime2.22
/LCD_B2: LCD-4,3in_DISP1.23, LCD-5in_DISP1.23, LCD-7in_DISP1.17, LCD-7in_DISP2.17, LCD-10,1in_DISP1.17, LCD-10,1in_DISP2.17, LCD_CON1.23, LCD_FLAT_CON1.23, LCD_Lime1.23, LCD_Lime2.23
/LCD_B3: LCD-4,3in_DISP1.24, LCD-5in_DISP1.24, LCD-7in_DISP1.16, LCD-7in_DISP2.16, LCD-10,1in_DISP1.16, LCD-10,1in_DISP2.16, LCD_CON1.24, LCD_FLAT_CON1.24, LCD_Lime1.24, LCD_Lime2.24
/LCD_B4: LCD-4,3in_DISP1.25, LCD-5in_DISP1.25, LCD-7in_DISP1.15, LCD-7in_DISP2.15, LCD-10,1in_DISP1.15, LCD-10,1in_DISP2.15, LCD_CON1.25, LCD_FLAT_CON1.25, LCD_Lime1.25, LCD_Lime2.25
/LCD_B5: LCD-4,3in_DISP1.26, LCD-5in_DISP1.26, LCD-7in_DISP1.14, LCD-7in_DISP2.14, LCD-10,1in_DISP1.14, LCD-10,1in_DISP2.14, LCD_CON1.26, LCD_FLAT_CON1.26, LCD_Lime1.26, LCD_Lime2.26
/LCD_B6: LCD-4,3in_DISP1.27, LCD-5in_DISP1.27, LCD-7in_DISP1.13, LCD-7in_DISP2.13, LCD-10,1in_DISP1.13, LCD-10,1in_DISP2.13, LCD_CON1.27, LCD_FLAT_CON1.27, LCD_Lime1.27, LCD_Lime2.27
/LCD_B7: LCD-4,3in_DISP1.28, LCD-5in_DISP1.28, LCD-7in_DISP1.12, LCD-7in_DISP2.12, LCD-10,1in_DISP1.12, LCD-10,1in_DISP2.12, LCD_CON1.28, LCD_FLAT_CON1.28, LCD_Lime1.28, LCD_Lime2.28
/LCD_BKL: LCD_CON1.36, LCD_FLAT_CON1.36, LCD_Lime1.36, LCD_Lime2.36, R49.1, R50.1
/LCD_CLK: LCD-4,3in_DISP1.30, LCD-5in_DISP1.30, LCD-7in_DISP1.37, LCD-7in_DISP2.37, LCD-10,1in_DISP1.37, LCD-10,1in_DISP2.37, LCD_CON1.31, LCD_FLAT_CON1.31, LCD_Lime1.31, LCD_Lime2.31
/LCD_DE: LCD-4,3in_DISP1.34, LCD-5in_DISP1.34, LCD-7in_DISP1.9, LCD-7in_DISP2.9, LCD-10,1in_DISP1.9, LCD-10,1in_DISP2.9, LCD_CON1.32, LCD_FLAT_CON1.32, LCD_Lime1.32, LCD_Lime2.32, R3.2, R19.2
/LCD_G0: LCD-4,3in_DISP1.13, LCD-5in_DISP1.13, LCD-7in_DISP1.27, LCD-7in_DISP2.27, LCD-10,1in_DISP1.27, LCD-10,1in_DISP2.27, LCD_CON1.13, LCD_FLAT_CON1.13, LCD_Lime1.13, LCD_Lime2.13
/LCD_G1: LCD-4,3in_DISP1.14, LCD-5in_DISP1.14, LCD-7in_DISP1.26, LCD-7in_DISP2.26, LCD-10,1in_DISP1.26, LCD-10,1in_DISP2.26, LCD_CON1.14, LCD_FLAT_CON1.14, LCD_Lime1.14, LCD_Lime2.14
/LCD_G2: LCD-4,3in_DISP1.15, LCD-5in_DISP1.15, LCD-7in_DISP1.25, LCD-7in_DISP2.25, LCD-10,1in_DISP1.25, LCD-10,1in_DISP2.25, LCD_CON1.15, LCD_FLAT_CON1.15, LCD_Lime1.15, LCD_Lime2.15
/LCD_G3: LCD-4,3in_DISP1.16, LCD-5in_DISP1.16, LCD-7in_DISP1.24, LCD-7in_DISP2.24, LCD-10,1in_DISP1.24, LCD-10,1in_DISP2.24, LCD_CON1.16, LCD_FLAT_CON1.16, LCD_Lime1.16, LCD_Lime2.16
/LCD_G4: LCD-4,3in_DISP1.17, LCD-5in_DISP1.17, LCD-7in_DISP1.23, LCD-7in_DISP2.23, LCD-10,1in_DISP1.23, LCD-10,1in_DISP2.23, LCD_CON1.17, LCD_FLAT_CON1.17, LCD_Lime1.17, LCD_Lime2.17, R59.2, R60.2
/LCD_G5: LCD-4,3in_DISP1.18, LCD-5in_DISP1.18, LCD-7in_DISP1.22, LCD-7in_DISP2.22, LCD-10,1in_DISP1.22, LCD-10,1in_DISP2.22, LCD_CON1.18, LCD_FLAT_CON1.18, LCD_Lime1.18, LCD_Lime2.18, R56.2, R57.2
/LCD_G6: LCD-4,3in_DISP1.19, LCD-5in_DISP1.19, LCD-7in_DISP1.21, LCD-7in_DISP2.21, LCD-10,1in_DISP1.21, LCD-10,1in_DISP2.21, LCD_CON1.19, LCD_FLAT_CON1.19, LCD_Lime1.19, LCD_Lime2.19, R53.2, R54.2
/LCD_G7: LCD-4,3in_DISP1.20, LCD-5in_DISP1.20, LCD-7in_DISP1.20, LCD-7in_DISP2.20, LCD-10,1in_DISP1.20, LCD-10,1in_DISP2.20, LCD_CON1.20, LCD_FLAT_CON1.20, LCD_Lime1.20, LCD_Lime2.20, R51.2, R52.2
/LCD_HSYNC: LCD-4,3in_DISP1.32, LCD-5in_DISP1.32, LCD-7in_DISP1.11, LCD-7in_DISP2.11, LCD-10,1in_DISP1.11, LCD-10,1in_DISP2.11, LCD_CON1.29, LCD_FLAT_CON1.29, LCD_Lime1.29, LCD_Lime2.29, R5.2, R21.2
/LCD_L/R: L/R_EN1.1, LCD_CON1.33, LCD_FLAT_CON1.33, LCD_Lime1.33, LCD_Lime2.33
/LCD_PWRE: CTRL/EN1.3, LCD_CON1.35, LCD_FLAT_CON1.35, LCD_Lime1.35, LCD_Lime2.35
/LCD_R0: LCD-4,3in_DISP1.5, LCD-5in_DISP1.5, LCD-7in_DISP1.35, LCD-7in_DISP2.35, LCD-10,1in_DISP1.35, LCD-10,1in_DISP2.35, LCD_CON1.5, LCD_FLAT_CON1.5, LCD_Lime1.5, LCD_Lime2.5
/LCD_R1: LCD-4,3in_DISP1.6, LCD-5in_DISP1.6, LCD-7in_DISP1.34, LCD-7in_DISP2.34, LCD-10,1in_DISP1.34, LCD-10,1in_DISP2.34, LCD_CON1.6, LCD_FLAT_CON1.6, LCD_Lime1.6, LCD_Lime2.6
/LCD_R2: LCD-4,3in_DISP1.7, LCD-5in_DISP1.7, LCD-7in_DISP1.33, LCD-7in_DISP2.33, LCD-10,1in_DISP1.33, LCD-10,1in_DISP2.33, LCD_CON1.7, LCD_FLAT_CON1.7, LCD_Lime1.7, LCD_Lime2.7
/LCD_R3: LCD-4,3in_DISP1.8, LCD-5in_DISP1.8, LCD-7in_DISP1.32, LCD-7in_DISP2.32, LCD-10,1in_DISP1.32, LCD-10,1in_DISP2.32, LCD_CON1.8, LCD_FLAT_CON1.8, LCD_Lime1.8, LCD_Lime2.8
/LCD_R4: LCD-4,3in_DISP1.9, LCD-5in_DISP1.9, LCD-7in_DISP1.31, LCD-7in_DISP2.31, LCD-10,1in_DISP1.31, LCD-10,1in_DISP2.31, LCD_CON1.9, LCD_FLAT_CON1.9, LCD_Lime1.9, LCD_Lime2.9
/LCD_R5: LCD-4,3in_DISP1.10, LCD-5in_DISP1.10, LCD-7in_DISP1.30, LCD-7in_DISP2.30, LCD-10,1in_DISP1.30, LCD-10,1in_DISP2.30, LCD_CON1.10, LCD_FLAT_CON1.10, LCD_Lime1.10, LCD_Lime2.10
/LCD_R6: LCD-4,3in_DISP1.11, LCD-5in_DISP1.11, LCD-7in_DISP1.29, LCD-7in_DISP2.29, LCD-10,1in_DISP1.29, LCD-10,1in_DISP2.29, LCD_CON1.11, LCD_FLAT_CON1.11, LCD_Lime1.11, LCD_Lime2.11
/LCD_R7: LCD-4,3in_DISP1.12, LCD-5in_DISP1.12, LCD-7in_DISP1.28, LCD-7in_DISP2.28, LCD-10,1in_DISP1.28, LCD-10,1in_DISP2.28, LCD_CON1.12, LCD_FLAT_CON1.12, LCD_Lime1.12, LCD_Lime2.12
/LCD_U/D: LCD_CON1.34, LCD_FLAT_CON1.34, LCD_Lime1.34, LCD_Lime2.34, U/D_EN1.1
/LCD_VSYNC: LCD-4,3in_DISP1.33, LCD-5in_DISP1.33, LCD-7in_DISP1.10, LCD-7in_DISP2.10, LCD-10,1in_DISP1.10, LCD-10,1in_DISP2.10, LCD_CON1.30, LCD_FLAT_CON1.30, LCD_Lime1.30, LCD_Lime2.30, R4.2, R20.2
/RTP-X1/~CTP-INT: LCD-5in_CTP1.4, LCD-7in_CTP1.4, LCD-10,1in_CTP1.3, LCD_CON1.37, LCD_FLAT_CON1.37, LCD_Lime1.37, LCD_Lime2.37, R29.1, R30.1, U1.9
/RTP-X2/~CTP-RST: LCD-5in_CTP1.1, LCD-7in_CTP1.3, LCD-10,1in_CTP1.6, LCD_CON1.38, LCD_FLAT_CON1.38, LCD_Lime1.38, LCD_Lime2.38, R28.1, R31.1
/RTP-Y1/CTP-SCL: LCD-5in_CTP1.6, LCD-7in_CTP1.2, LCD-10,1in_CTP1.4, LCD_CON1.39, LCD_FLAT_CON1.39, LCD_Lime1.39, LCD_Lime2.39, R27.1, R32.1, U1.11, U2.6
/RTP-Y2/CTP-SDA: LCD-5in_CTP1.5, LCD-7in_CTP1.1, LCD-10,1in_CTP1.5, LCD_CON1.40, LCD_FLAT_CON1.40, LCD_Lime1.40, LCD_Lime2.40, R26.1, R33.1, U1.13, U2.5
AVDD: C19.1, D4.1, LCD-7in_DISP1.43, LCD-7in_DISP2.43, LCD-10,1in_DISP1.43, LCD-10,1in_DISP2.43, PWR1.2, R15.1, R37.1, R44.2, U4.2
GND: C1.2, C2.2, C3.2, C4.1, C5.2, C6.2, C7.2, C8.2, C9.1, C10.1, C11.2, C12.1, C13.1, C15.1, C16.2, C17.2, C18.1, C19.2, C21.2, C24.1, C25.2, C26.1, C27.2, D1.2, D3.2, D5.2, D6.2, D7.1, LCD-4,3in_DISP1.0, LCD-4,3in_DISP1.3, LCD-4,3in_DISP1.29, LCD-4,3in_DISP1.36, LCD-5in_CTP1.0, LCD-5in_CTP1.3, LCD-5in_DISP1.0, LCD-5in_DISP1.3, LCD-5in_DISP1.29, LCD-5in_DISP1.36, LCD-7in_CTP1.0, LCD-7in_CTP1.5, LCD-7in_DISP1.0, LCD-7in_DISP1.5, LCD-7in_DISP1.36, LCD-7in_DISP1.38, LCD-7in_DISP1.48, LCD-7in_DISP2.0, LCD-7in_DISP2.5, LCD-7in_DISP2.36, LCD-7in_DISP2.38, LCD-7in_DISP2.48, LCD-7in_RTP1.0, LCD-10,1in_CTP1.0, LCD-10,1in_CTP1.1, LCD-10,1in_DISP1.0, LCD-10,1in_DISP1.5, LCD-10,1in_DISP1.36, LCD-10,1in_DISP1.38, LCD-10,1in_DISP1.48, LCD-10,1in_DISP2.0, LCD-10,1in_DISP2.5, LCD-10,1in_DISP2.36, LCD-10,1in_DISP2.38, LCD-10,1in_DISP2.48, LCD-10,1in_RTP1.0, LCD_CON1.2, LCD_CON1.4, LCD_FLAT_CON1.0, LCD_FLAT_CON1.2, LCD_FLAT_CON1.4, LCD_Lime1.2, LCD_Lime1.4, LCD_Lime2.2, LCD_Lime2.4, PWR1.10, PWR_JACK1.2, R2.1, R3.1, R8.1, R9.1, R10.1, R12.1, R14.1, R16.1, R18.1, R19.1, R24.1, R35.1, R37.2, R38.1, R40.1, R45.1, R52.1, R54.1, R57.1, R58.1, R60.1, T1.2, U1.2, U1.3, U1.4, U1.7, U1.8, U1.14, U1.17, U1.20, U2.1, U2.2, U2.3, U2.4, U2.7, U3.5, U4.5
L/R: L/R_EN1.2, LCD-7in_DISP1.39, LCD-7in_DISP2.39, LCD-10,1in_DISP1.39, LCD-10,1in_DISP2.39, R11.1, R12.2
unnamed: C4.2, LCD-7in_DISP1.44, LCD-7in_DISP2.44, R6.2
unnamed: C9.2, LCD-10,1in_DISP1.44, LCD-10,1in_DISP2.44, R22.2
unnamed: C14.2, D2.1, FET1.1, R34.1
unnamed: C16.1, U3.2, VLED+_E1.2
unnamed: C18.2, D4.2, R39.1
unnamed: C20.1, FET2.2, FET3.2, PWR_JACK1.1, R42.2, R63.2
unnamed: C20.2, D2.2, FET2.1, R42.1
unnamed: C21.1, R43.1, R46.2, R47.2
unnamed: C22.1, D4.3
unnamed: C22.2, C23.1, L2.1, U4.4
unnamed: C23.2, D6.3
unnamed: C24.2, D6.1, R55.1
unnamed: CTRL/EN1.2, T1.1
unnamed: D2.3, R36.2
unnamed: D5.1, R47.1, R50.2
unnamed: FET3.1, PWR_JACK1.3, R63.1, R64.1
unnamed: L1.1, U3.4
unnamed: LCD-7in_DISP1.8, LCD-7in_DISP2.8, R1.2, R2.2
unnamed: LCD-7in_DISP1.45, LCD-7in_DISP2.45
unnamed: LCD-7in_DISP1.47, LCD-7in_DISP2.47, R7.2, R8.2
unnamed: LCD-7in_DISP1.49, LCD-7in_DISP2.49
unnamed: LCD-7in_DISP1.50, LCD-7in_DISP2.50
unnamed: LCD-10,1in_DISP1.8, LCD-10,1in_DISP2.8, R17.2, R18.2
unnamed: LCD-10,1in_DISP1.45, LCD-10,1in_DISP2.45
unnamed: LCD-10,1in_DISP1.47, LCD-10,1in_DISP2.47, R23.2, R24.2
unnamed: LCD-10,1in_DISP1.49, LCD-10,1in_DISP2.49
unnamed: LCD-10,1in_DISP1.50, LCD-10,1in_DISP2.50
unnamed: R25.2, U1.5
unnamed: R36.1, T1.3
unnamed: R38.2, R40.2, R41.2, VLED-_E1.2
unnamed: R41.1, R43.2, U3.6
unnamed: R44.1, R45.2, U4.6
unnamed: R48.2, R49.2, U3.1
RTP_X+(X2): LCD-4,3in_DISP1.37, LCD-5in_DISP1.37, LCD-7in_RTP1.3, LCD-10,1in_RTP1.3, R31.2, U1.18
RTP_X-(X1): C12.2, LCD-4,3in_DISP1.39, LCD-5in_DISP1.39, LCD-7in_RTP1.1, LCD-10,1in_RTP1.1, R25.1, R30.2, U1.19
RTP_Y+(Y2): LCD-4,3in_DISP1.40, LCD-5in_DISP1.40, LCD-7in_RTP1.4, LCD-10,1in_RTP1.4, R33.2, U1.15
RTP_Y-(Y1): C13.2, LCD-4,3in_DISP1.38, LCD-5in_DISP1.38, LCD-7in_RTP1.2, LCD-10,1in_RTP1.2, R32.2, U1.16
U/D: LCD-7in_DISP1.40, LCD-7in_DISP2.40, LCD-10,1in_DISP1.40, LCD-10,1in_DISP2.40, R13.1, R14.2, U/D_EN1.2
VCOM: C6.1, D1.1, LCD-7in_DISP1.6, LCD-7in_DISP1.46, LCD-7in_DISP2.6, LCD-7in_DISP2.46, LCD-10,1in_DISP1.6, LCD-10,1in_DISP1.46, LCD-10,1in_DISP2.6, LCD-10,1in_DISP2.46, PWR1.5, R15.2, R16.2
VDD: 3.3V/5.0V1.2, C25.1, C27.1, L1.2, L2.2, PWR1.4, R48.1, U3.3, U4.1, U4.3
VGH: C15.2, D3.1, LCD-7in_DISP1.41, LCD-7in_DISP2.41, LCD-10,1in_DISP1.41, LCD-10,1in_DISP2.41, PWR1.1, R35.2, R39.2
VGL: C26.2, D7.2, LCD-7in_DISP1.42, LCD-7in_DISP2.42, LCD-10,1in_DISP1.42, LCD-10,1in_DISP2.42, PWR1.7, R55.2, R58.2
VLED+: LCD-4,3in_DISP1.2, LCD-5in_DISP1.2, LCD-7in_DISP1.1, LCD-7in_DISP1.2, LCD-7in_DISP2.1, LCD-7in_DISP2.2, LCD-10,1in_DISP1.1, LCD-10,1in_DISP1.2, LCD-10,1in_DISP2.1, LCD-10,1in_DISP2.2, PWR1.8, VLED+_E1.1
VLED-: LCD-4,3in_DISP1.1, LCD-5in_DISP1.1, LCD-7in_DISP1.3, LCD-7in_DISP1.4, LCD-7in_DISP2.3, LCD-7in_DISP2.4, LCD-10,1in_DISP1.3, LCD-10,1in_DISP1.4, LCD-10,1in_DISP2.3, LCD-10,1in_DISP2.4, PWR1.9, VLED-_E1.1

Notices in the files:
HARDWARE/LCDs/LCD-DRIVER/Hardware revision C/LCD-DRIVER_Rev_C.kicad_pcb:
(C) 2018
HARDWARE/Lime2-SATA/Lime2-SATA_RevA/Lime2-SATA_RevA.kicad_pcb:
(c) 2019
